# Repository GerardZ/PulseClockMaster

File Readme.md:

## PulseClock Master

TAGS: slaveClock slave-clock pulseclock pulse-clock secondary-clock slave clock impulse driver masterclock 

### So what is this

This is a NTP-clock which can drive a Pulse Clock/ secondary clock/ slave clock, the type of clock found in schools, stations or other big buildings. Nowadays most of them have been replaced by modern ones, but they still exists. These clocks are driven by a master clock which pulses the slave clocks every minute, where it moves the minute-hand one minute. So it acts as a masterclock for these slave clocks.
<div align="center"></div>
Webpage is a mere indication of the clock, time is displayed and is coming from the ESP, it is not your pc`s time (though they should be the same). Date is displayed and there is a red dot in the top right corner which displays the state of the pulse, on = poitive, off = negative.

### Why would i need this

You might be a happy owner of such a slave clock, threw it on your attic, like me.  Always asking yourself how to enable that beautiful thing. This can be your savior. 
My Clock:<div></div>

### What do i need

*   A slave clock obviously
*   This circuitry
*   ESP01 programmer (dont let this frighten you, its a no-brainer)
*   Wifi & internet

### The Circuit

Circuit consist of a 24V power module, 3v3 step down module, an ESP01, opamp & 2 transistor driver.

<div align="center"></div>

We need a 24V pulse to drive the clock. Pulses are given every minute where one pulse is positive, the next negative, this is done by the opamp, buffer transistors and the output electrolitic capacitors. The ESP01 pulses the opamp by AND-ing the lsb of the minutes every minute.
Internally time is handled by NTP so we never need to worry over adjusting except for power outages. Even DST is handled !
When you have multiple clocks, you probably get away with two or three, not tested. You could rise capacitance of the output capacitors by 2x 1000uF.
I am running one clock but have only installed one 470uF capacitor. That should give an indication. But I guess not all clock brands have the same load.

### The software

ESP01 firmware has a wifi portal, NTP, a webserver displaying time and pulse status. Time is updated through websockets to the webpage so even for this simple application there is already a lot going on. See for yourself !

### Using

Supply with mains, connect your clock, power up.
On first connection there will be no wifi credentials so the device will go into portal mode and starts is own wifi station with SSID: PulseClockMaster, connect to it (pw: 12345678) and open a page on your webbrowser. The portal page should come up. Enter your wifi credentials an press save. The device will reboot and connect, hopefully, to your wifi. From thereon you should be able to connect via http://PulseClockMaster.local but this depends on your router. If not try
http://PulseClockMaster. If that doesnt work still, find out what ip it is given by your router and connect via ip.
There is only a display of time and date, so this step is not even necessary but it will give you a good idea that it is all functioning well.

You will have to adjust time b hand on the physical clock once. From thereon it will be synced every minute. If you notice the clock keeps behind one minute, reverse polary on the clock and re-adjust. The latter is only nececaity once since the clock pulses depend on wether the minute is odd or even.

You only have to re-adjust after a power-failure.

### Todo\`s

*   make settings for other timezones & DST settings, now only changeable in code
*   power outage handling ?

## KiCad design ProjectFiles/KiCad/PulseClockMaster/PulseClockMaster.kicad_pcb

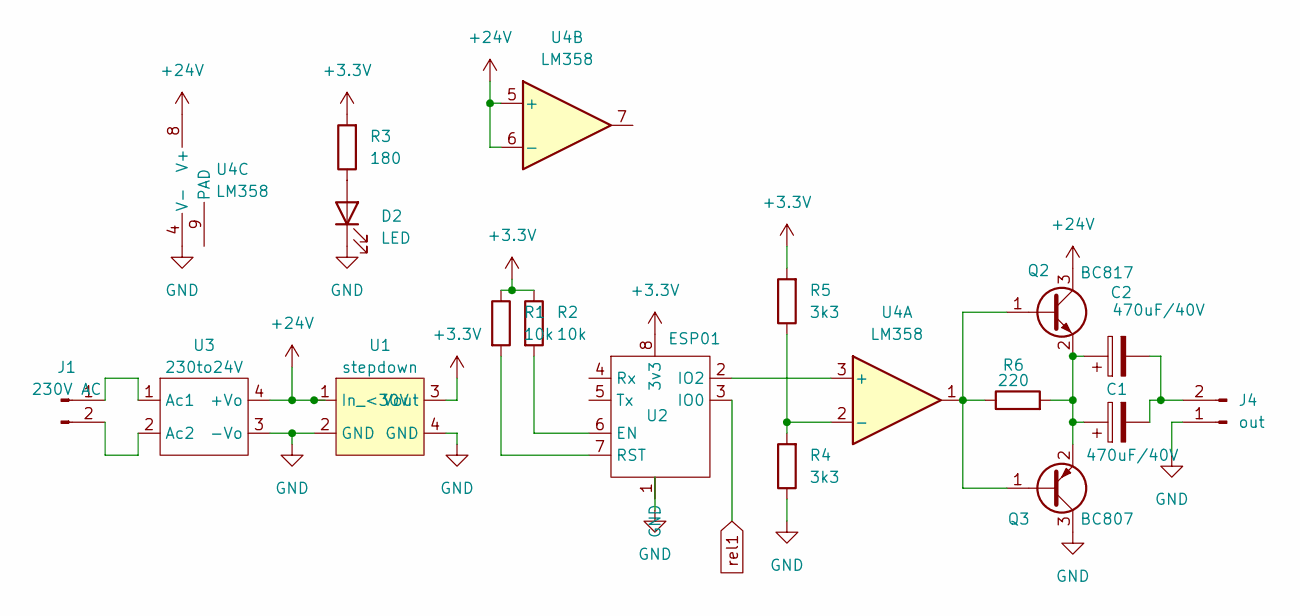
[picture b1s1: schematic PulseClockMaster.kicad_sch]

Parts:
C1, C2: 470uF/40V; CP_Radial_D8.0mm_P3.80mm
D2: LED; LED_D5.0mm
J1: 230V AC; TerminalBlock_MaiXu_MX126-5.0-02P_1x02_P5.00mm
J4: out; TerminalBlock_4Ucon_1x02_P3.50mm_Horizontal
Q2: BC817; SOT-23
Q3: BC807; SOT-23
R1, R2: 10k; R_0805_2012Metric_Pad1.20x1.40mm_HandSolder
R3: 180; R_0805_2012Metric_Pad1.20x1.40mm_HandSolder
R4, R5: 3k3; R_0805_2012Metric_Pad1.20x1.40mm_HandSolder
R6: 220; R_0805_2012Metric_Pad1.20x1.40mm_HandSolder
U1: stepdown; Mini-Stepdown
U2: ESP01; ESP01_conn+outline
U3: 230to24V; Mini Ac-DC 230 to 24V module EBAY
U4: LM358; SOIC-8_3.9x4.9mm_P1.27mm

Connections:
+3.3V: R1.1, R2.1, R3.2, R5.2, U1.3 (Vout), U2.8 (3v3)
+24V: Q2.3 (C), U1.1 (In_<30V), U3.4 (+Vo), U4.5 (+), U4.6 (-), U4.8 (V+)
GND: D2.1 (K), J4.1, Q3.3 (C), R4.1, U1.2 (GND), U1.4 (GND), U2.1 (GND), U3.3 (-Vo), U4.4 (V-)
unnamed: D2.2 (A), R3.1
unnamed: J1.1, U3.1 (Ac1)
unnamed: J1.2, U3.2 (Ac2)
unnamed: C1.2, C2.2, J4.2
unnamed: Q2.1 (B), Q3.1 (B), R6.1, U4.1
unnamed: C1.1, C2.1, Q2.2 (E), Q3.2 (E), R6.2
unnamed: R2.2, U2.6 (EN)
unnamed: U2.2 (IO2), U4.3 (+)
unnamed: R1.2, U2.7 (RST)
unnamed: R4.2, R5.1, U4.2 (-)
rel1: U2.3 (IO0)

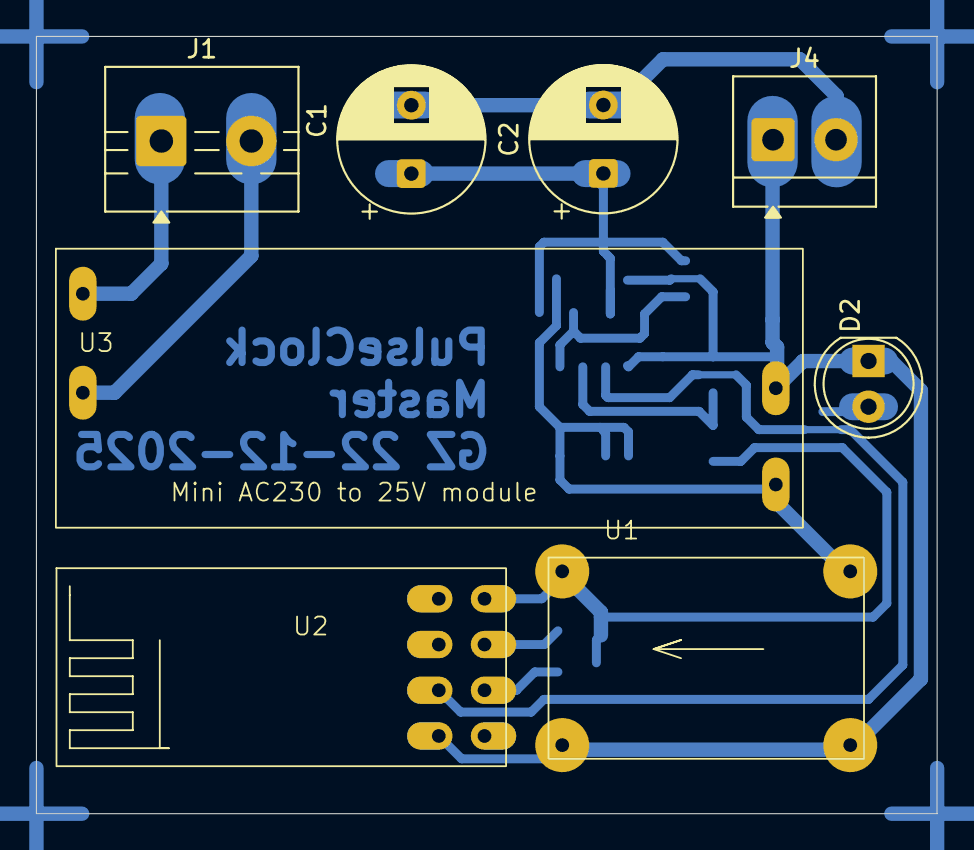
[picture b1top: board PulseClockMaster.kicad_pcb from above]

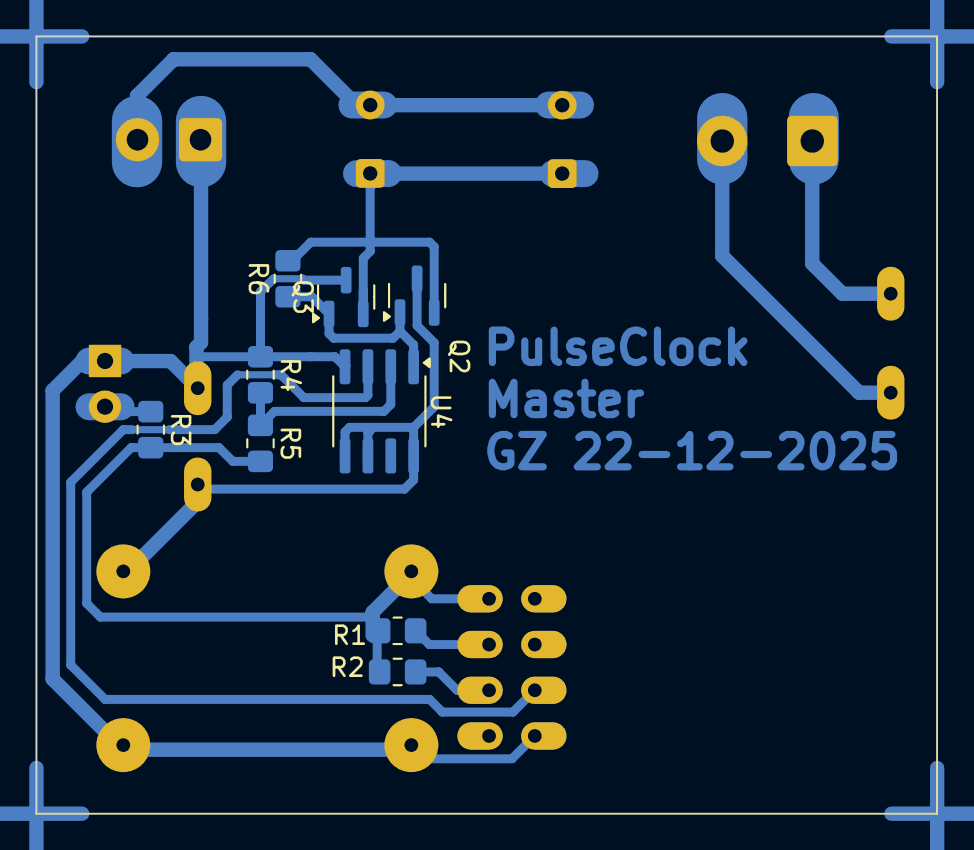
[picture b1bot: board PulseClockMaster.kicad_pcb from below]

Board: 2 copper layers, 50.0 x 43.2 mm, 17 parts (9 on the bottom side), 13 nets.

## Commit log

2025-12-21 Init
2025-12-21 readme
2025-12-22 Added PCB
2025-12-22 readme update
2025-12-22 typos
2025-12-22 issue in PCB
2025-12-24 PCB & Javascript updates
2025-12-24 image
2025-12-24 image3
2025-12-26 centerd
2025-12-27 DST handling (not tested)
2025-12-27 Readme update, small PCB update
2025-12-30 some cleanup
2026-01-02 housing added
2026-01-03 favicon made smaller
2026-01-10 cleanup
2026-05-03 linux update
